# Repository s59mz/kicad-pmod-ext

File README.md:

# kicad-pmod-ext
PMOD Extension Cable

Schematic:
[kicad-pmod-ext.pdf](kicad-pmod-ext.pdf)

BOM:
[kicad-pmod-ext.csv](kicad-pmod-ext.csv)

Gerbers:
[gerbers.zip](https://github.com/s59mz/kicad-pmod-ext/raw/main/gerbers.zip)

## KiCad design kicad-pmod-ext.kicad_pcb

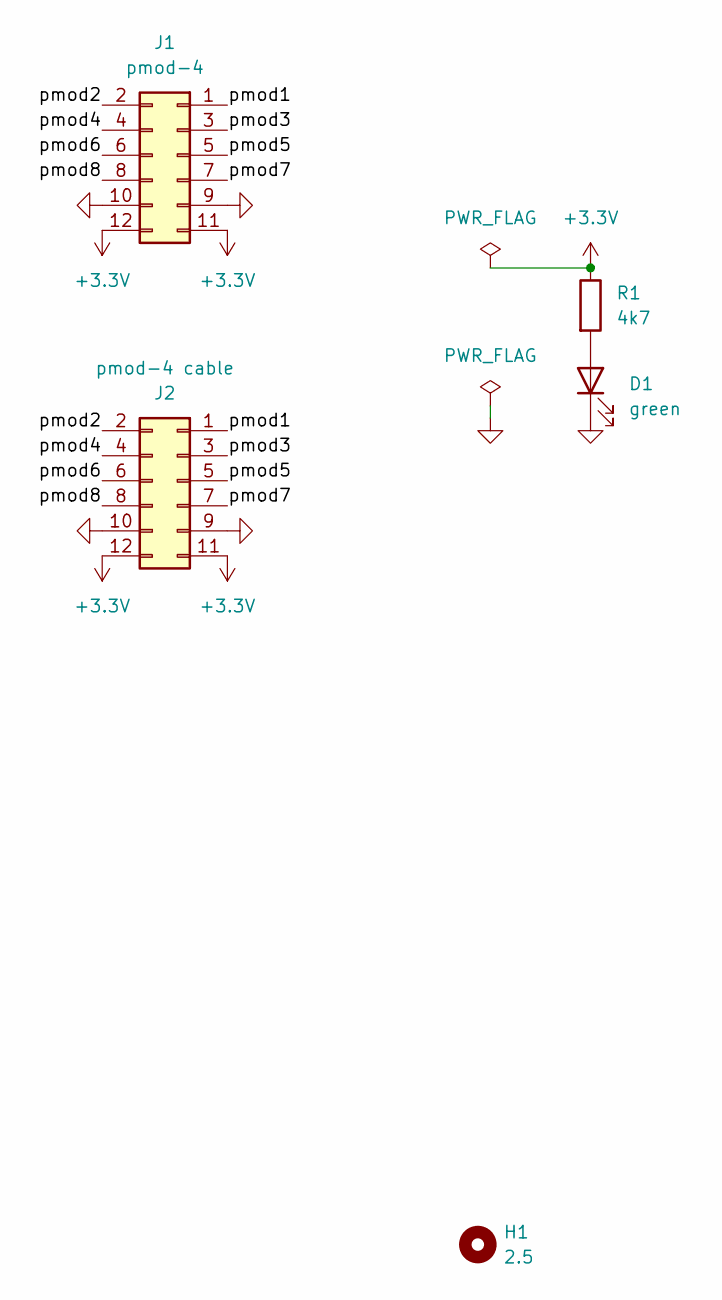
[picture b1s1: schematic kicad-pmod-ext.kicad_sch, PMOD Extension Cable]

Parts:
D1: green; LED_0603_1608Metric_Pad1.05x0.95mm_HandSolder
H1: 2.5; MountingHole_2.5mm
J1: pmod-4; PinHeader_2x06_P2.54mm_Horizontal
J2: pmod-4 cable; PinSocket_2x06_P2.54mm_Vertical
R1: 4k7; R_0603_1608Metric_Pad0.98x0.95mm_HandSolder

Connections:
+3.3V: J1.11, J1.12, J2.11, J2.12, R1.1
/pmod1: J1.1, J2.1
/pmod2: J1.2, J2.2
/pmod3: J1.3, J2.3
/pmod4: J1.4, J2.4
/pmod5: J1.5, J2.5
/pmod6: J1.6, J2.6
/pmod7: J1.7, J2.7
/pmod8: J1.8, J2.8
GND: D1.1 (K), J1.9, J1.10, J2.9, J2.10
unnamed: D1.2 (A), R1.2

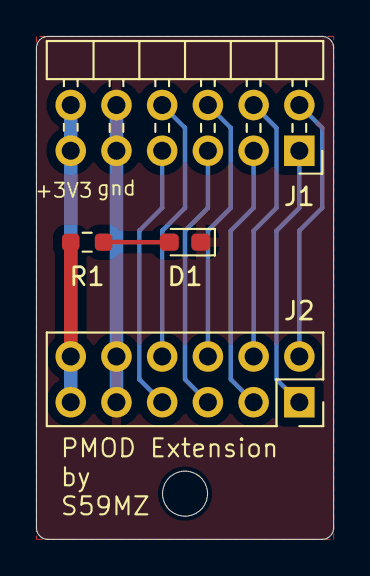
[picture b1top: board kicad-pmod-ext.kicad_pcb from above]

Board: 2 copper layers, 16.5 x 27.9 mm, 5 parts (0 on the bottom side), 11 nets.
